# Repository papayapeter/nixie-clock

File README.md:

# nixie-clock
a nixie clock built around 4 IN-2 tubes and an INS-1 dot

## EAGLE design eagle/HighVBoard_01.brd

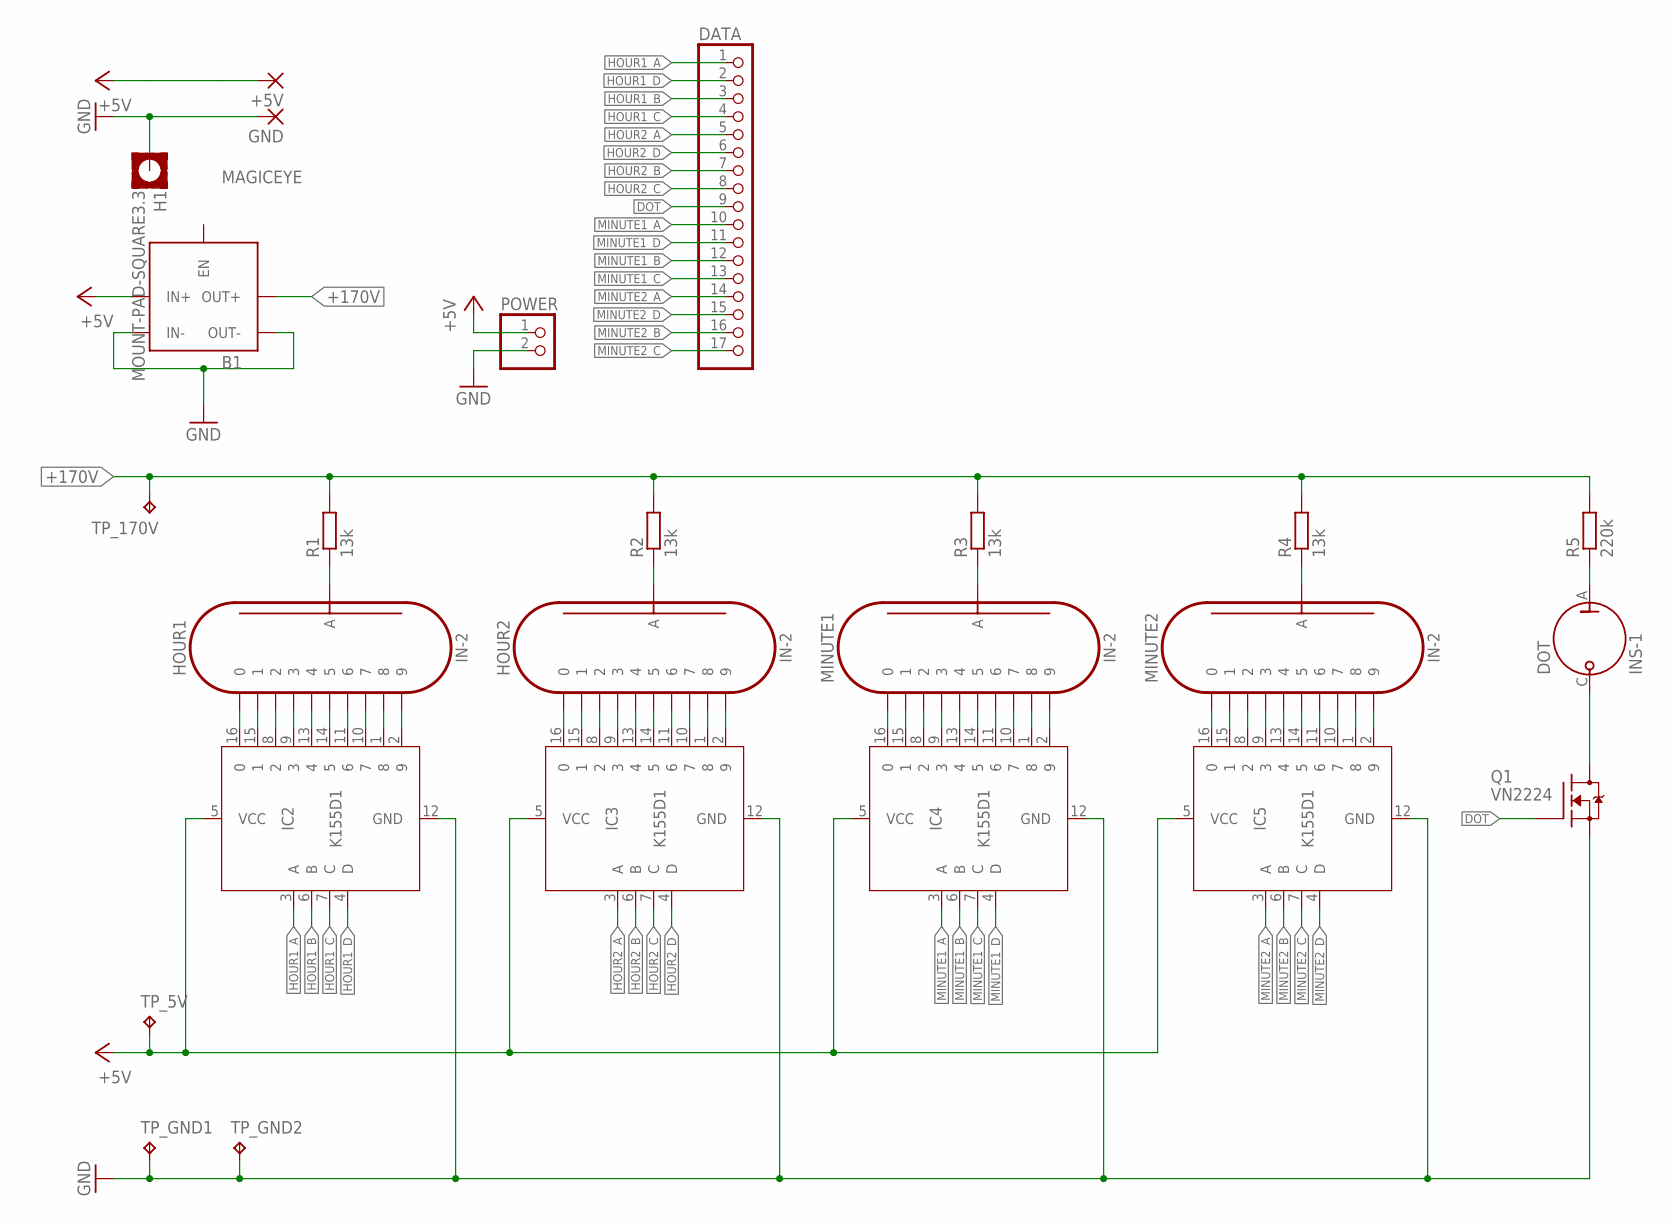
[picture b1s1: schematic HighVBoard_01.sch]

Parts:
+5V: 2,15/1,0
B1: MAGICEYE
DATA: PINHD-1X17; 1X17
DOT: INS-1
GND: 2,15/1,0
H1: MOUNT-PAD-SQUARE3.3; 3,3-PAD-SQUARE
HOUR1, HOUR2: IN-2
IC2, IC3, IC4, IC5: K155D1; DIL16
MINUTE1, MINUTE2: IN-2
POWER: PINHD-1X2; 1X02
Q1: VN2224; TO92
R1, R2, R3, R4: 13k; 0207/10
R5: 220k; 0207/10
TP_5V, TP_170V: TPPAD1-13; P1-13
TP_GND1, TP_GND2: TPPAD1-13; P1-13

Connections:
+5V: +5V.1, B1.IN+, IC2.5 (VCC), IC3.5 (VCC), IC4.5 (VCC), IC5.5 (VCC), POWER.1, TP_5V.TP
+170V: B1.OUT+, R1.2, R2.2, R3.2, R4.2, R5.2, TP_170V.TP
DOT: DATA.9, Q1.2 (G)
GND: B1.IN-, B1.OUT-, GND.1, H1.B3,3, IC2.12 (GND), IC3.12 (GND), IC4.12 (GND), IC5.12 (GND), POWER.2, Q1.1 (S), TP_GND1.TP, TP_GND2.TP
HOUR1_A: DATA.1, IC2.3 (A)
HOUR1_B: DATA.3, IC2.6 (B)
HOUR1_C: DATA.4, IC2.7 (C)
HOUR1_D: DATA.2, IC2.4 (D)
HOUR2_A: DATA.5, IC3.3 (A)
HOUR2_B: DATA.7, IC3.6 (B)
HOUR2_C: DATA.8, IC3.7 (C)
HOUR2_D: DATA.6, IC3.4 (D)
MINUTE1_A: DATA.10, IC4.3 (A)
MINUTE1_B: DATA.12, IC4.6 (B)
MINUTE1_C: DATA.13, IC4.7 (C)
MINUTE1_D: DATA.11, IC4.4 (D)
MINUTE2_A: DATA.14, IC5.3 (A)
MINUTE2_B: DATA.16, IC5.6 (B)
MINUTE2_C: DATA.17, IC5.7 (C)
MINUTE2_D: DATA.15, IC5.4 (D)
unnamed: DOT.C, Q1.3 (D)
unnamed: HOUR1.0, IC2.16 (0)
unnamed: HOUR1.1, IC2.15 (1)
unnamed: HOUR1.2, IC2.8 (2)
unnamed: HOUR1.3, IC2.9 (3)
unnamed: HOUR1.4, IC2.13 (4)
unnamed: HOUR1.5, IC2.14 (5)
unnamed: HOUR1.6, IC2.11 (6)
unnamed: HOUR1.7, IC2.10 (7)
unnamed: HOUR1.8, IC2.1 (8)
unnamed: HOUR1.9, IC2.2 (9)
unnamed: HOUR1.A, R1.1
unnamed: HOUR2.0, IC3.16 (0)
unnamed: HOUR2.1, IC3.15 (1)
unnamed: HOUR2.2, IC3.8 (2)
unnamed: HOUR2.3, IC3.9 (3)
unnamed: HOUR2.4, IC3.13 (4)
unnamed: HOUR2.5, IC3.14 (5)
unnamed: HOUR2.6, IC3.11 (6)
unnamed: HOUR2.7, IC3.10 (7)
unnamed: HOUR2.8, IC3.1 (8)
unnamed: HOUR2.9, IC3.2 (9)
unnamed: HOUR2.A, R2.1
unnamed: IC4.16 (0), MINUTE1.0
unnamed: IC4.15 (1), MINUTE1.1
unnamed: IC4.8 (2), MINUTE1.2
unnamed: IC4.9 (3), MINUTE1.3
unnamed: IC4.13 (4), MINUTE1.4
unnamed: IC4.14 (5), MINUTE1.5
unnamed: IC4.11 (6), MINUTE1.6
unnamed: IC4.10 (7), MINUTE1.7
unnamed: IC4.1 (8), MINUTE1.8
unnamed: IC4.2 (9), MINUTE1.9
unnamed: MINUTE1.A, R3.1
unnamed: IC5.16 (0), MINUTE2.0
unnamed: IC5.15 (1), MINUTE2.1
unnamed: IC5.8 (2), MINUTE2.2
unnamed: IC5.9 (3), MINUTE2.3
unnamed: IC5.13 (4), MINUTE2.4
unnamed: IC5.14 (5), MINUTE2.5
unnamed: IC5.11 (6), MINUTE2.6
unnamed: IC5.10 (7), MINUTE2.7
unnamed: IC5.1 (8), MINUTE2.8
unnamed: IC5.2 (9), MINUTE2.9
unnamed: MINUTE2.A, R4.1
unnamed: DOT.A, R5.1

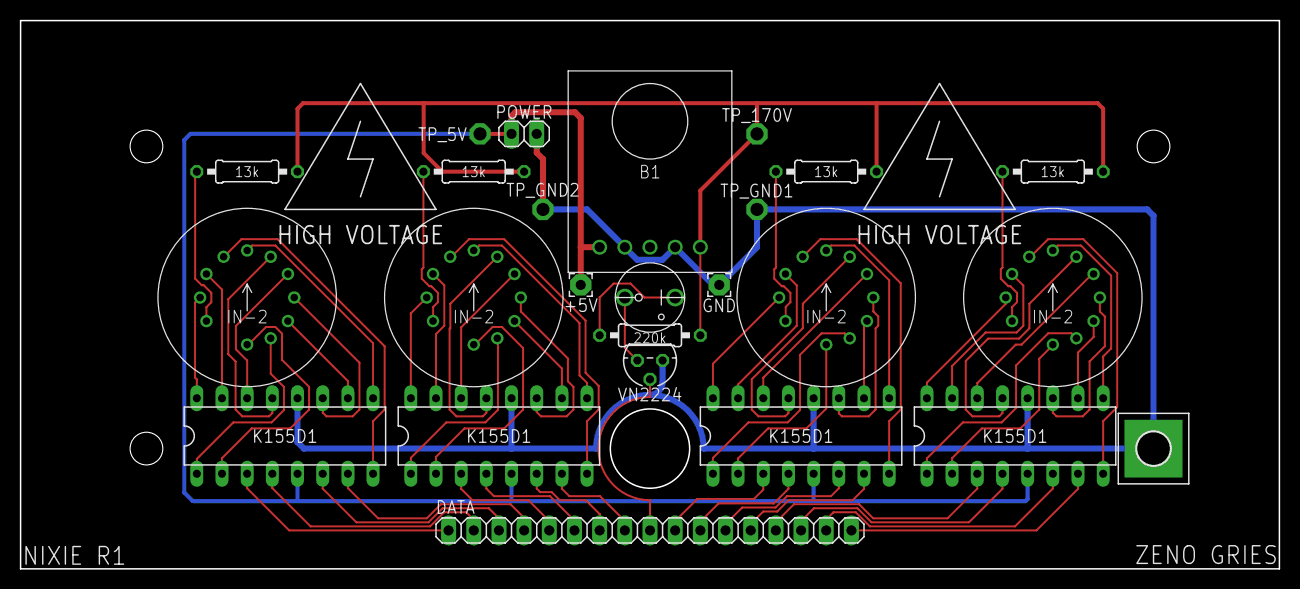
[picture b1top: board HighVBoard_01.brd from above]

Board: 2 copper layers, 127.0 x 55.3 mm, 25 parts (0 on the bottom side), 66 nets.

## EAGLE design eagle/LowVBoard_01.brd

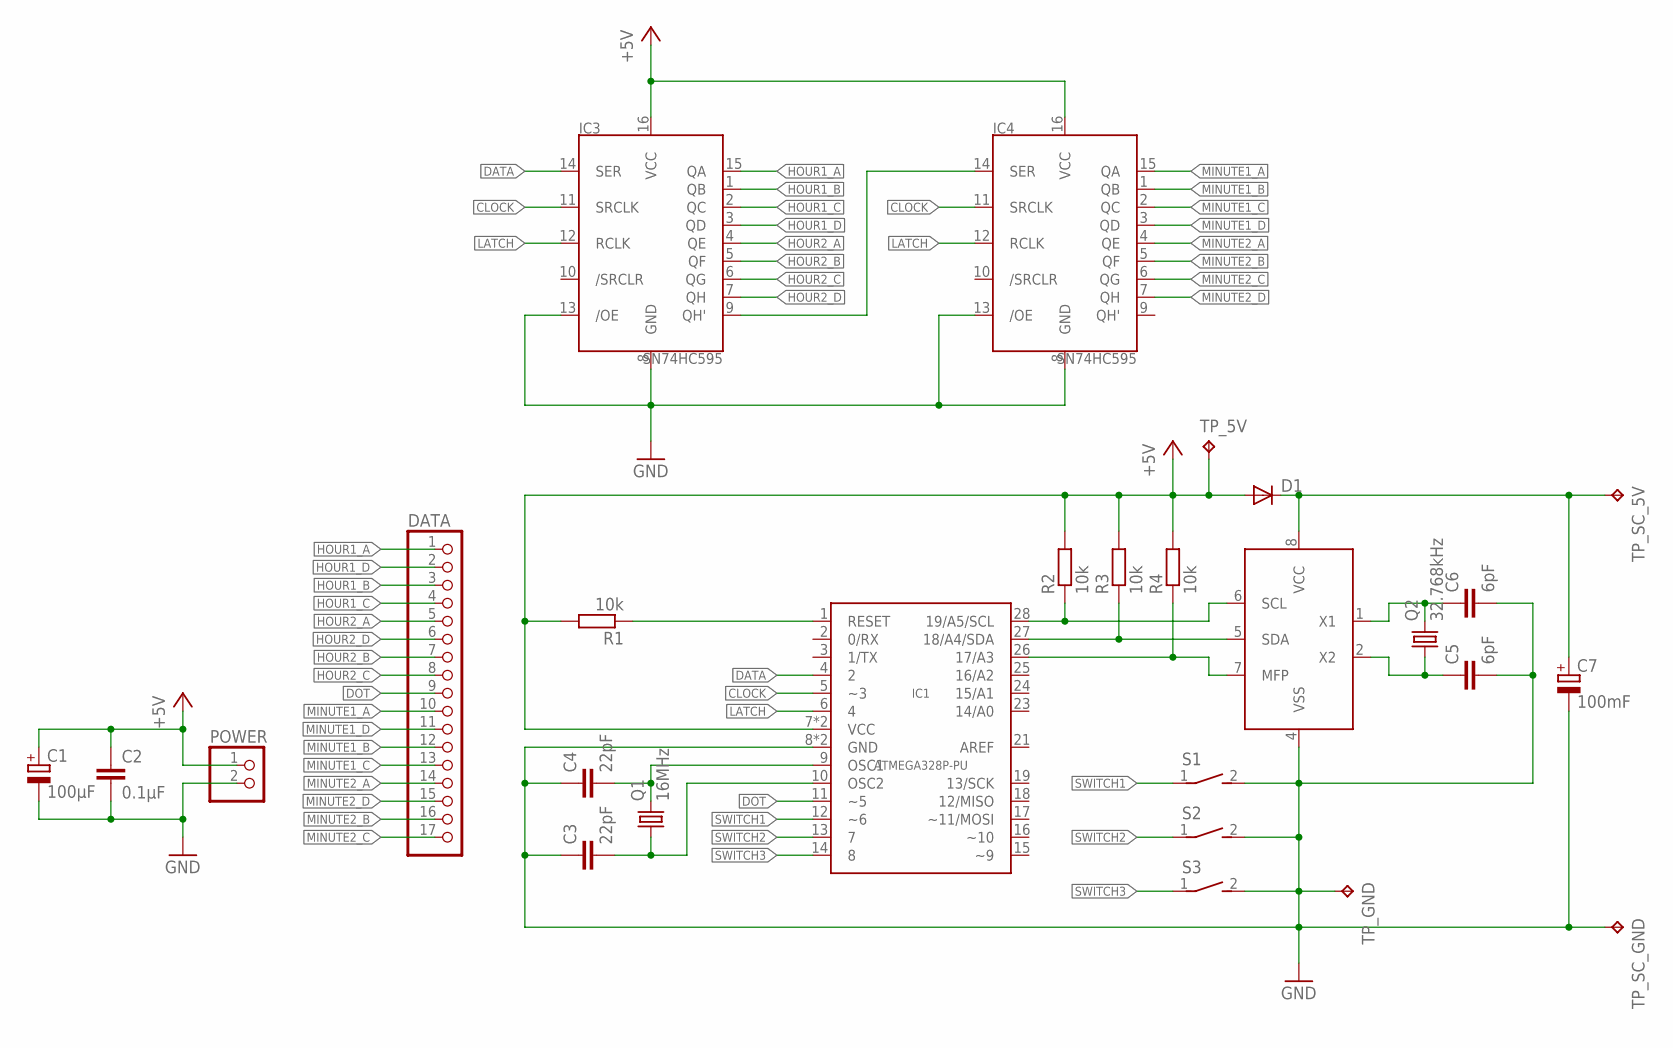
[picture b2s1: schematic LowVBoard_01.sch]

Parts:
C1: 100µF; E2-5
C2: 0.1µF; C025-024X044
C3, C4: 22pF; C025-024X044
C5, C6: 6pF; C025-024X044
C7: 100mF; SUPERCAP-11.5
D1: DIODE-DO201-15; DO201-15
DATA: PINHD-1X17; 1X17
IC1: ATMEGA328P-PU; DIP28
IC2: MCP7940M; DIL8
IC3, IC4: SN74HC595; DIL16
POWER: PINHD-1X2; 1X02
Q1: 16MHz; HC49/S
Q2: 32.768kHz; CFS-206
R1, R2, R3, R4: 10k; 0207/7
S1, S2, S3: GPTS203211B
TP_5V: TPPAD1-13; P1-13
TP_GND: TPPAD1-13; P1-13
TP_SC_5V: TPPAD1-13; P1-13
TP_SC_GND: TPPAD1-13; P1-13

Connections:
+5V: C1.+, C2.1, D1.A, IC1.7 (VCC), IC1.20 (VCC), IC3.16 (VCC), IC4.16 (VCC), POWER.1, R1.2, R2.2, R3.2, R4.2, TP_5V.TP
CLOCK: IC1.5 (~3), IC3.11 (SRCLK), IC4.11 (SRCLK)
DATA: IC1.4 (2), IC3.14 (SER)
DOT: DATA.9, IC1.11 (~5)
GND: C1.-, C2.2, C3.1, C4.1, C5.2, C6.2, C7.-, IC1.8 (GND), IC1.22 (GND), IC2.4 (VSS), IC3.8 (GND), IC3.13 (/OE), IC4.8 (GND), IC4.13 (/OE), POWER.2, S1.2 (S), S2.2 (S), S3.2 (S), TP_GND.TP, TP_SC_GND.TP
HOUR1_A: DATA.1, IC3.15 (QA)
HOUR1_B: DATA.3, IC3.1 (QB)
HOUR1_C: DATA.4, IC3.2 (QC)
HOUR1_D: DATA.2, IC3.3 (QD)
HOUR2_A: DATA.5, IC3.4 (QE)
HOUR2_B: DATA.7, IC3.5 (QF)
HOUR2_C: DATA.8, IC3.6 (QG)
HOUR2_D: DATA.6, IC3.7 (QH)
LATCH: IC1.6 (4), IC3.12 (RCLK), IC4.12 (RCLK)
MINUTE1_A: DATA.10, IC4.15 (QA)
MINUTE1_B: DATA.12, IC4.1 (QB)
MINUTE1_C: DATA.13, IC4.2 (QC)
MINUTE1_D: DATA.11, IC4.3 (QD)
MINUTE2_A: DATA.14, IC4.4 (QE)
MINUTE2_B: DATA.16, IC4.5 (QF)
MINUTE2_C: DATA.17, IC4.6 (QG)
MINUTE2_D: DATA.15, IC4.7 (QH)
unnamed: C7.+, D1.C, IC2.8 (VCC), TP_SC_5V.TP
unnamed: C4.2, IC1.9 (OSC1), Q1.2
unnamed: C3.2, IC1.10 (OSC2), Q1.1
unnamed: IC1.1 (RESET), R1.1
unnamed: IC1.28 (19/A5/SCL), IC2.6 (SCL), R2.1
unnamed: IC1.27 (18/A4/SDA), IC2.5 (SDA), R3.1
unnamed: IC1.26 (17/A3), IC2.7 (MFP), R4.1
unnamed: C6.1, IC2.1 (X1), Q2.P$2 (2)
unnamed: C5.1, IC2.2 (X2), Q2.P$1 (1)
unnamed: IC3.9 (QH'), IC4.14 (SER)
SWITCH1: IC1.12 (~6), S1.1
SWITCH2: IC1.13 (7), S2.1
SWITCH3: IC1.14 (8), S3.1

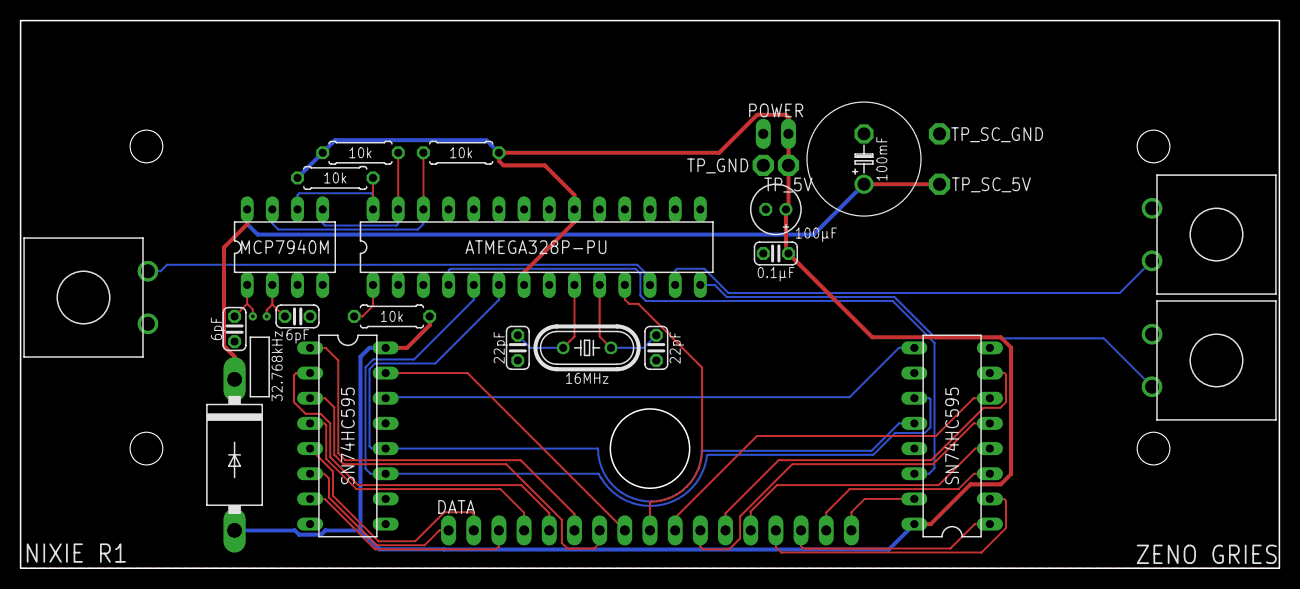
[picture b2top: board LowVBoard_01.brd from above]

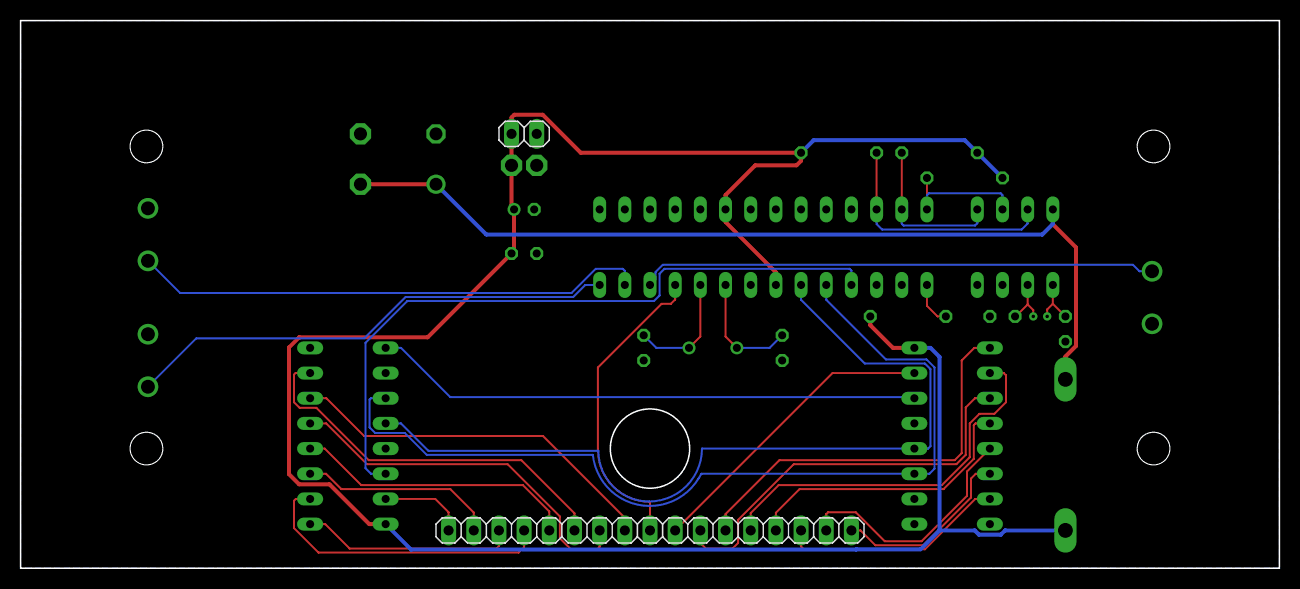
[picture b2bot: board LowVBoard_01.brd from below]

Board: 2 copper layers, 127.0 x 55.2 mm, 27 parts (2 on the bottom side), 35 nets.

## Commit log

2019-07-09 start
2019-07-10 sourced clock Class out
2019-07-10 created clock library
2019-07-10 formatting
2019-07-10 changed constructor
2019-07-10 commented serial out
2019-08-15 added tests
2019-10-23 cleaned up
2020-08-03 added images
2020-08-03 changed directory
2023-09-19 new board
